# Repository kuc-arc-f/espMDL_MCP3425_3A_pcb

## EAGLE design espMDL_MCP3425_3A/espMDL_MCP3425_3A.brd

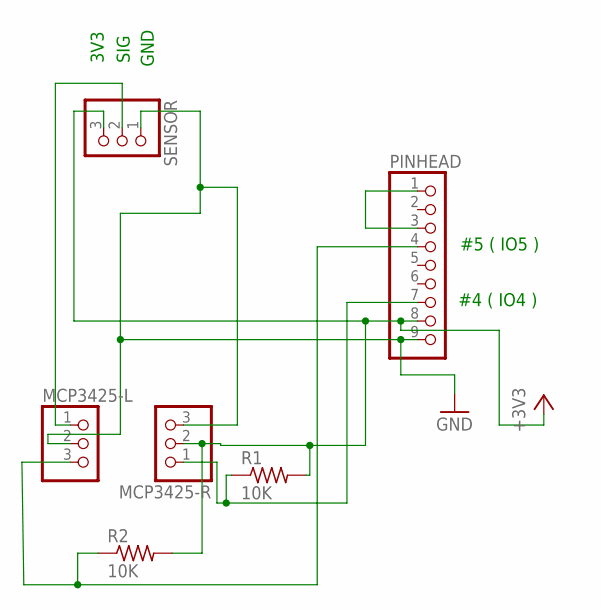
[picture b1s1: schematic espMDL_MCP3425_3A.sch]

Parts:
MCP3425-L, MCP3425-R: PINHD-1X3; 1X03
PINHEAD: PINHD-1X9; 1X09
R1, R2: 10K; 0204/7
SENSOR: PINHD-1X3; 1X03

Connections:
+3V3: MCP3425-R.2, PINHEAD.8, R1.2, R2.2, SENSOR.3
GND: MCP3425-L.2, MCP3425-R.3, PINHEAD.9, SENSOR.1
unnamed: PINHEAD.1, PINHEAD.3
unnamed: MCP3425-R.1, PINHEAD.7, R1.1
unnamed: MCP3425-L.1, SENSOR.2
unnamed: MCP3425-L.3, PINHEAD.4, R2.1

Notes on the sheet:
#4 ( IO4 )
#5 ( IO5 )
3V3
SIG
GND

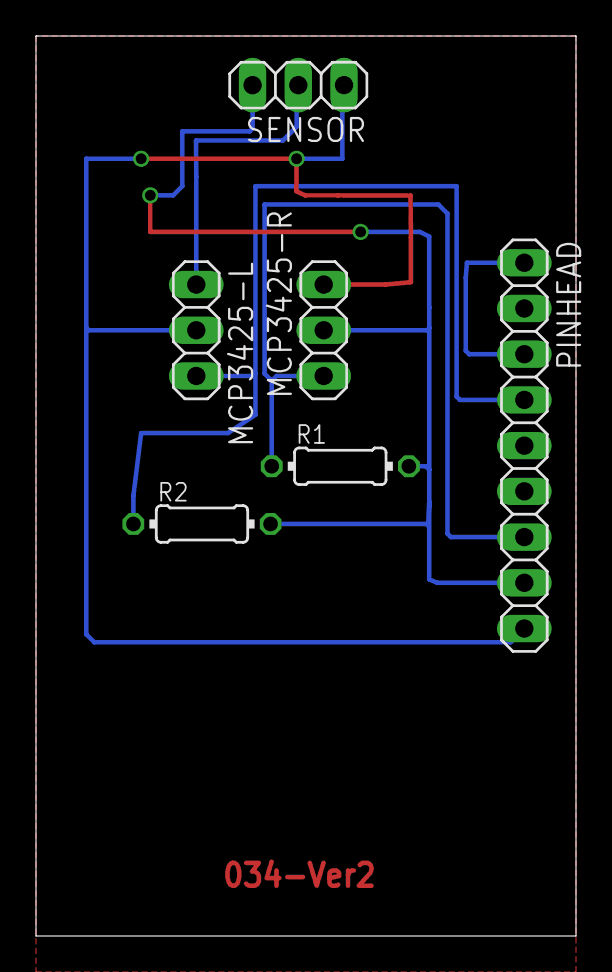
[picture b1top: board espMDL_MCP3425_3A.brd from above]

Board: 2 copper layers, 30.0 x 50.0 mm, 6 parts (0 on the bottom side), 6 nets.

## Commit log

2017-08-20 new, 08-20a1
